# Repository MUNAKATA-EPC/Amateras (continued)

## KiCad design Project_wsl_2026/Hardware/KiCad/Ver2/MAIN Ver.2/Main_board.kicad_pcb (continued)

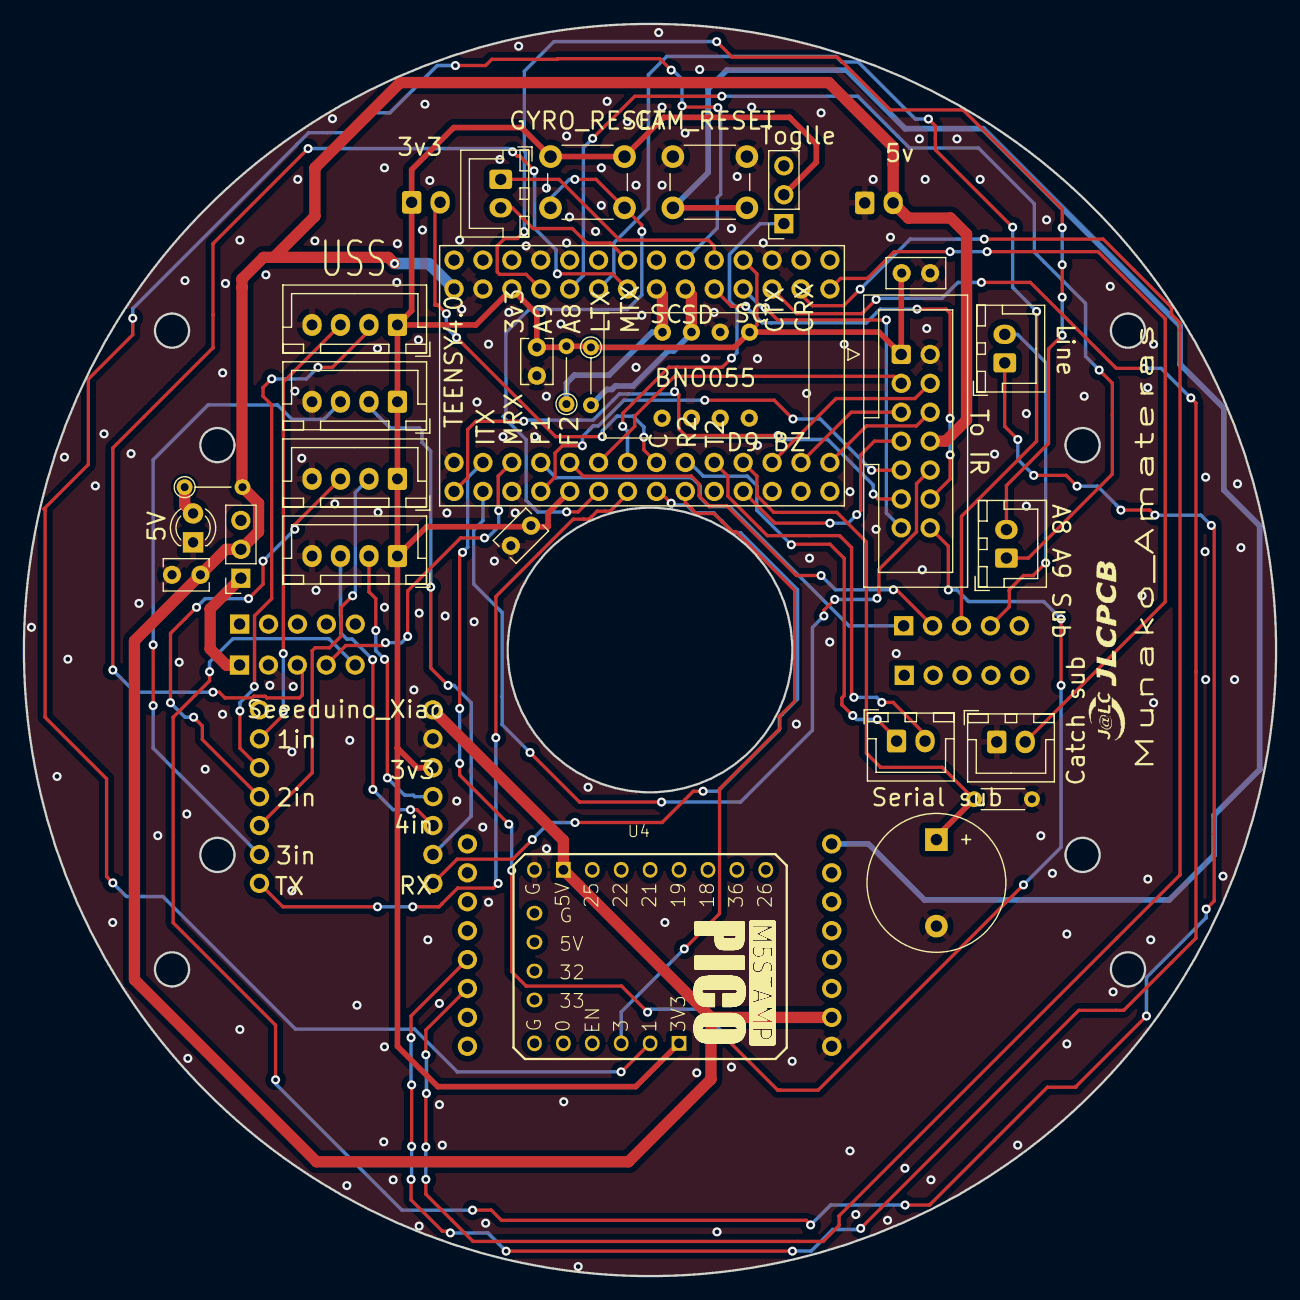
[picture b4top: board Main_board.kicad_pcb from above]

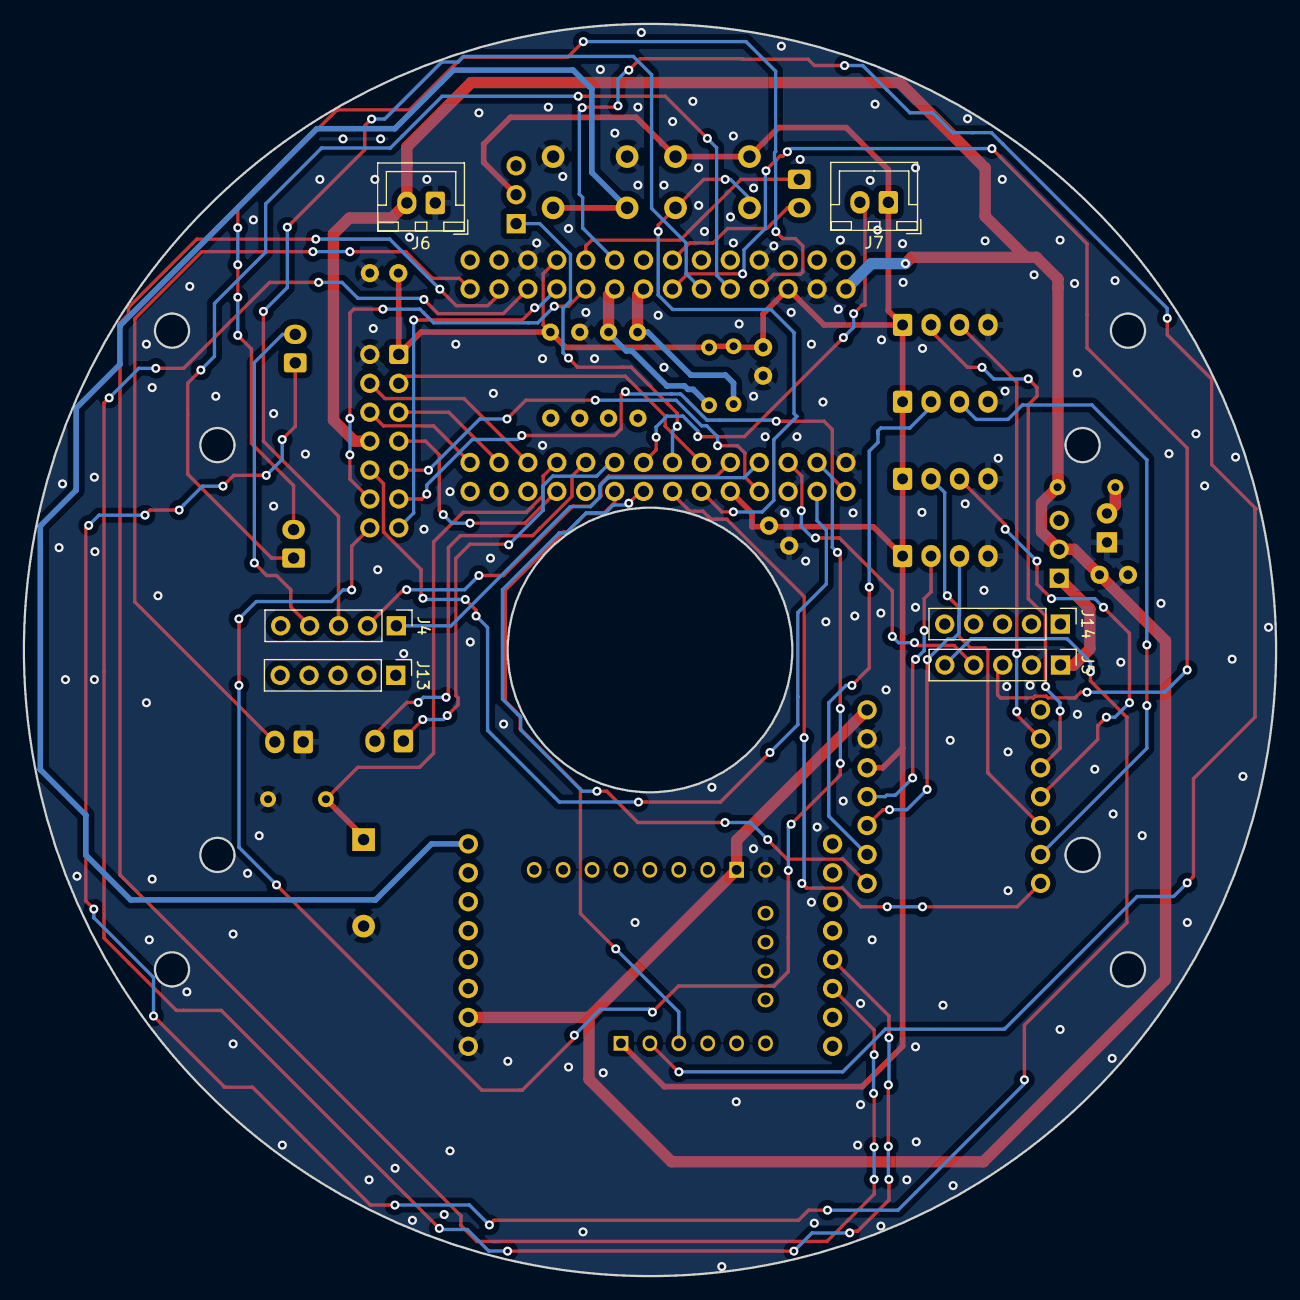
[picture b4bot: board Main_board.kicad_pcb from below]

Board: 2 copper layers, 110.0 x 110.0 mm, 35 parts (7 on the bottom side), 51 nets.

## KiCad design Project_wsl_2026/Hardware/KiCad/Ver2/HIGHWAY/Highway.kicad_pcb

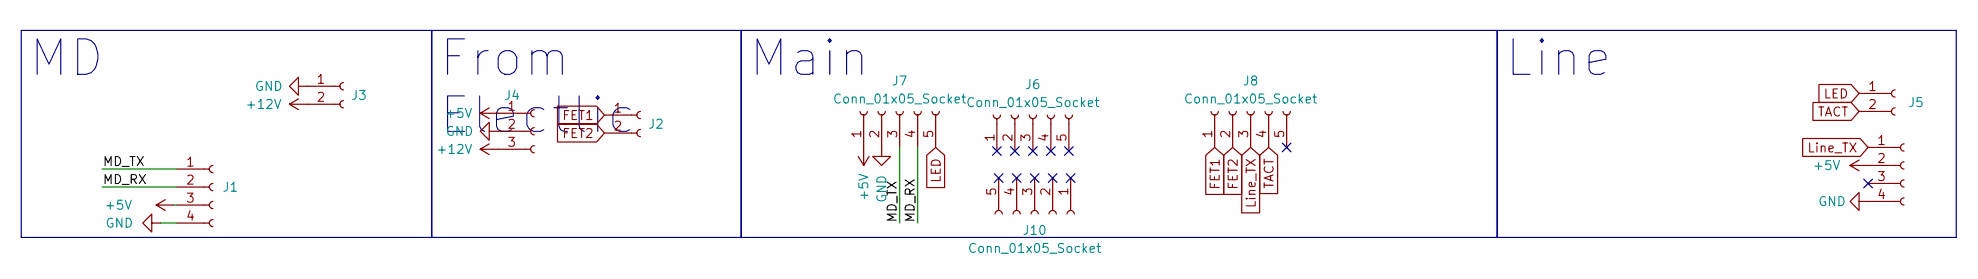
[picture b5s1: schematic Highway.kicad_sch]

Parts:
J1, J9: Conn_01x04_Socket; JST_XH_B4B-XH-A_1x04_P2.50mm_Vertical
J2, J3, J5: Conn_01x02_Socket; JST_XH_B2B-XH-A_1x02_P2.50mm_Vertical
J4: Conn_01x03_Socket; JST_XH_B3B-XH-A_1x03_P2.50mm_Vertical
J6, J7, J8, J10: Conn_01x05_Socket; PinSocket_1x05_P2.54mm_Vertical

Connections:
+5V: J1.3, J4.1, J7.1, J9.2
+12V: J3.2, J4.3
/MD_RX: J1.2, J7.4
/MD_TX: J1.1, J7.3
FET1: J2.1, J8.1
FET2: J2.2, J8.2
GND: J1.4, J3.1, J4.2, J7.2, J9.4
LED: J5.1, J7.5
Line_TX: J8.3, J9.1
TACT: J5.2, J8.4

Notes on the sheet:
From Electlic
Line
Main

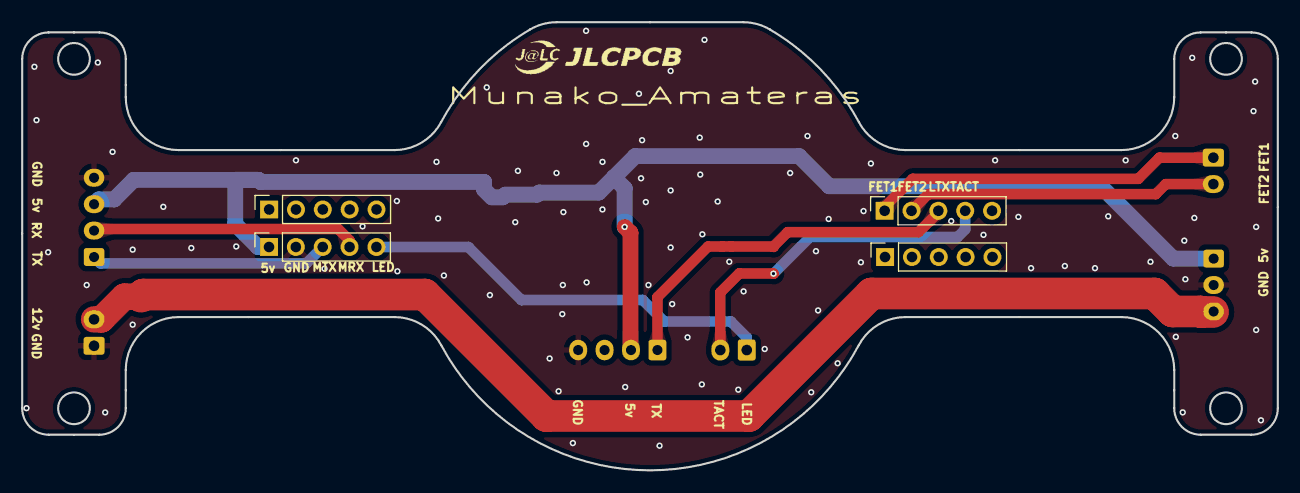
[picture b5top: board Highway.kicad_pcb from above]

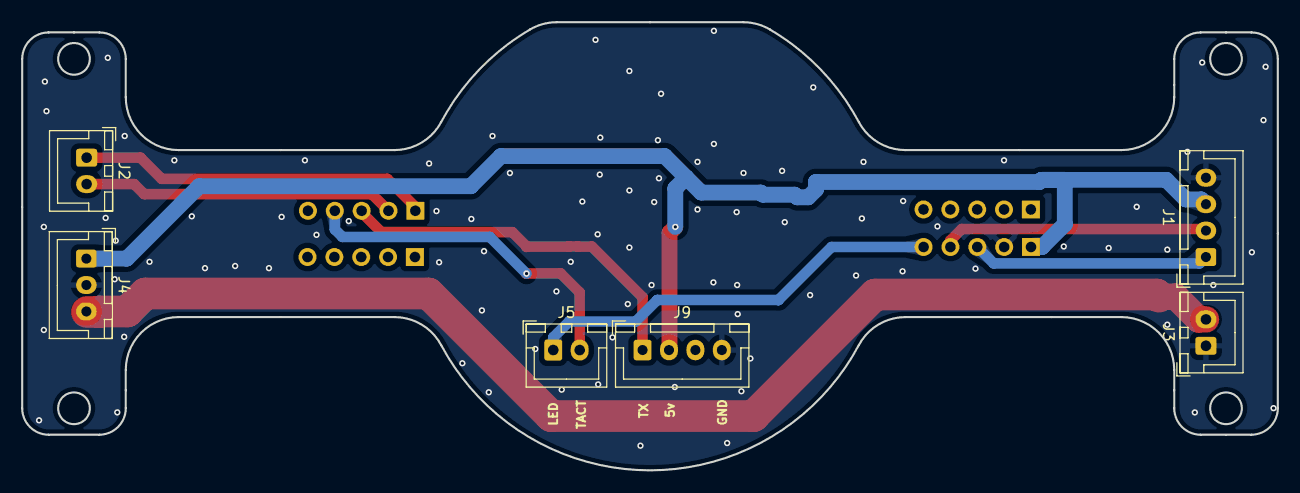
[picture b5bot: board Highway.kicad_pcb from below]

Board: 2 copper layers, 118.8 x 42.4 mm, 10 parts (6 on the bottom side), 10 nets.

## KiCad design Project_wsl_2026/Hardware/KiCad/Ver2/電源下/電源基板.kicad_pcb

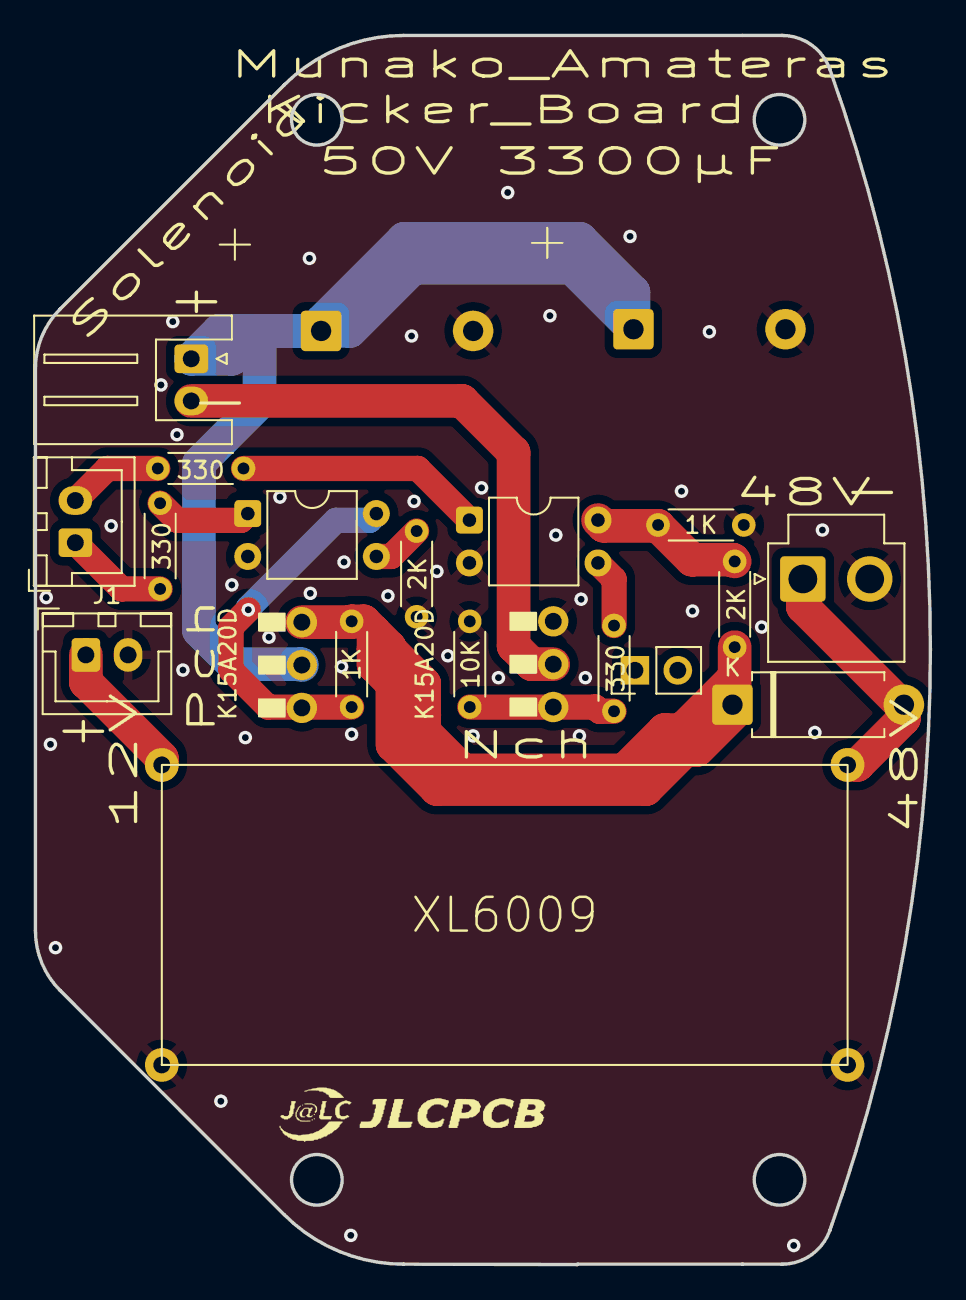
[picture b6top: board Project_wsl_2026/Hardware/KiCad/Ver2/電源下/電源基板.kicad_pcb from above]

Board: 2 copper layers, 53.0 x 72.8 mm, 21 parts (0 on the bottom side), 15 nets.

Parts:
1K, 1K#2: 1K; R_Axial_DIN0204_L3.6mm_D1.6mm_P5.08mm_Horizontal
2K, 2K#2: 2K; R_Axial_DIN0204_L3.6mm_D1.6mm_P5.08mm_Horizontal
10K: 10K; R_Axial_DIN0204_L3.6mm_D1.6mm_P5.08mm_Horizontal
330, 330#2, 330#3: 330; R_Axial_DIN0204_L3.6mm_D1.6mm_P5.08mm_Horizontal
C1, C4: C; 3300μF 50v
D2: D; D_DO-15_P10.16mm_Horizontal
FET: Conn_01x02_Socket; JST_XH_B2B-XH-A_1x02_P2.50mm_Vertical
J1: Conn_01x02_Socket; JST_XH_B2B-XH-A_1x02_P2.50mm_Vertical
J3: Conn_01x02_Socket; JST_VH_B2P-VH_1x02_P3.96mm_Vertical
J4: Conn_01x02_Socket; PinHeader_1x02_P2.54mm_Vertical
Q1: PMOS; K15A20D
Q2: NMOS; K15A20D
Solenoid: Conn_01x02_Socket; JST_XH_S2B-XH-A_1x02_P2.50mm_Horizontal
U2: XL6009
U3, U4: EL817; DIP-4_W7.62mm

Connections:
+12V: J1.1, U2.1 (IN＋)
+15V: 1K.1, 2K#2.2, U4.4
+48V: 1K#2.1, 2K#2.1, D2.1 (K), Q1.3 (S)
FET1: 330.1, FET.1
FET２: 330#3.1, FET.2
GND: 1K.2, 2K.2, 10K.2, C1.2, C4.2, J1.2, J3.2, Q2.3 (S), U2.2 (IN－), U2.4 (OUT－), U3.2, U4.2
unnamed: D2.2 (A), J3.1, U2.3 (OUT＋)
unnamed: 1K#2.2, Q1.2 (G), U3.4
unnamed: 10K.1, 330#2.1, Q2.2 (G)
unnamed: 330.2, U3.1
unnamed: 330#3.2, U4.1
unnamed: 2K.1, U3.3
unnamed: 330#2.2, U4.3
Solenoid+: C1.1, C4.1, Q1.1 (D), Solenoid.1
Solenoid-: Q2.1 (D), Solenoid.2

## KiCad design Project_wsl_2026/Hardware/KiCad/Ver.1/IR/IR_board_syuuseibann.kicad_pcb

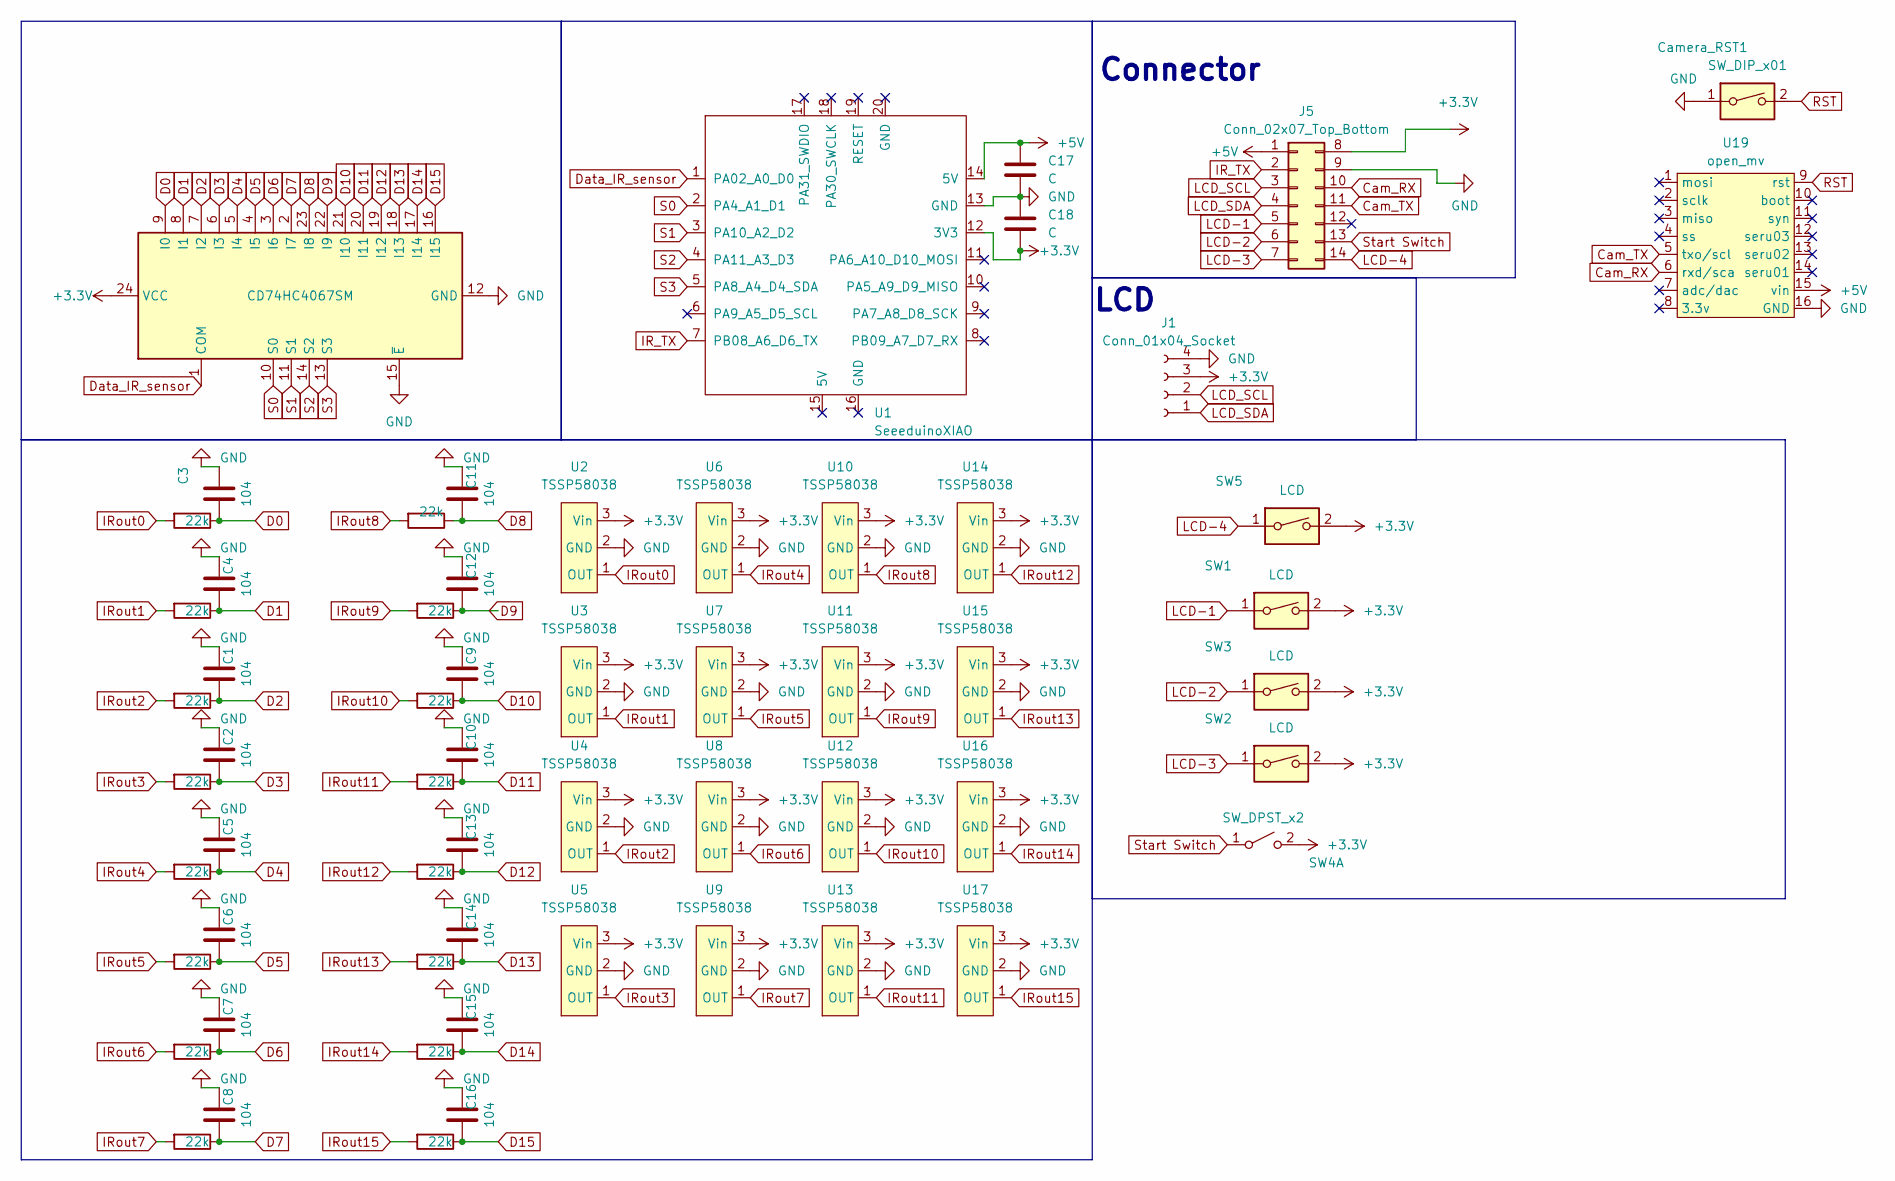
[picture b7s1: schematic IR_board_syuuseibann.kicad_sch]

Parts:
C1, C2, C3, C4, C5, C6, C7, C8, C9, C10, C11, C12, C13, C14, C15, C16: 104; C_0402_1005Metric; LCSC C1525
C17, C18: C; C_Disc_D5.0mm_W2.5mm_P2.50mm
Camera_RST1: SW_DIP_x01; SW_PUSH_6mm_H5mm
J1: Conn_01x04_Socket; PinHeader_1x04_P2.54mm_Vertical
J5: Conn_02x07_Top_Bottom; IDC-Header_2x07_P2.54mm_Vertical
R1, R2, R3, R4, R5, R6, R7, R8, R9, R10, R11, R12, R13, R14, R15, R16: 22k; R_0805_2012Metric; LCSC C25611
SW1, SW2, SW3, SW5: LCD; SW_PUSH_6mm_H5mm
SW4: SW_DPST_x2; PinSocket_1x03_P2.54mm_Vertical
U1: SeeeduinoXIAO; Seeeduino Xiao
U2, U3, U4, U5, U6, U7, U8, U9, U10, U11, U12, U13, U14, U15, U16, U17: TSSP58038; PinHeader_1x03_P2.54mm_Vertical
U18: CD74HC4067SM; SSOP-24_5.3x8.2mm_P0.65mm
U19: open_mv; Open MV

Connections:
+3.3V: C18.2, J1.3, J5.8, SW1.2, SW2.2, SW3.2, SW4.2 (B), SW5.2, U1.12 (3V3), U2.3 (Vin), U3.3 (Vin), U4.3 (Vin), U5.3 (Vin), U6.3 (Vin), U7.3 (Vin), U8.3 (Vin), U9.3 (Vin), U10.3 (Vin), U11.3 (Vin), U12.3 (Vin), U13.3 (Vin), U14.3 (Vin), U15.3 (Vin), U16.3 (Vin), U17.3 (Vin), U18.24 (VCC)
+5V: C17.1, J5.1, U1.14 (5V), U19.15 (vin)
Cam_RX: J5.10, U19.6 (rxd/sca)
Cam_TX: J5.11, U19.5 (txo/scl)
D0: C3.1, R3.1, U18.9 (I0)
D1: C4.1, R4.1, U18.8 (I1)
D2: C1.1, R1.1, U18.7 (I2)
D3: C2.1, R2.1, U18.6 (I3)
D4: C5.1, R5.1, U18.5 (I4)
D5: C6.1, R6.1, U18.4 (I5)
D6: C7.1, R7.1, U18.3 (I6)
D7: C8.1, R8.1, U18.2 (I7)
D8: C11.1, R11.1, U18.23 (I8)
D9: C12.1, R12.1, U18.22 (I9)
D10: C9.1, R9.1, U18.21 (I10)
D11: C10.1, R10.1, U18.20 (I11)
D12: C13.1, R13.1, U18.19 (I12)
D13: C14.1, R14.1, U18.18 (I13)
D14: C15.1, R15.1, U18.17 (I14)
D15: C16.1, R16.1, U18.16 (I15)
Data_IR_sensor: U1.1 (PA02_A0_D0), U18.1 (COM)
GND: C1.2, C2.2, C3.2, C4.2, C5.2, C6.2, C7.2, C8.2, C9.2, C10.2, C11.2, C12.2, C13.2, C14.2, C15.2, C16.2, C17.2, C18.1, Camera_RST1.1, J1.4, J5.9, U1.13 (GND), U2.2 (GND), U3.2 (GND), U4.2 (GND), U5.2 (GND), U6.2 (GND), U7.2 (GND), U8.2 (GND), U9.2 (GND), U10.2 (GND), U11.2 (GND), U12.2 (GND), U13.2 (GND), U14.2 (GND), U15.2 (GND), U16.2 (GND), U17.2 (GND), U18.12 (GND), U18.15 (~E), U19.16 (GND); also elsewhere on the board
IR_TX: J5.2, U1.7 (PB08_A6_D6_TX)
IRout0: R3.2, U2.1 (OUT)
IRout1: R4.2, U3.1 (OUT)
IRout2: R1.2, U4.1 (OUT)
IRout3: R2.2, U5.1 (OUT)
IRout4: R5.2, U6.1 (OUT)
IRout5: R6.2, U7.1 (OUT)
IRout6: R7.2, U8.1 (OUT)
IRout7: R8.2, U9.1 (OUT)
IRout8: R11.2, U10.1 (OUT)
IRout9: R12.2, U11.1 (OUT)
IRout10: R9.2, U12.1 (OUT)
IRout11: R10.2, U13.1 (OUT)
IRout12: R13.2, U14.1 (OUT)
IRout13: R14.2, U15.1 (OUT)
IRout14: R15.2, U16.1 (OUT)
IRout15: R16.2, U17.1 (OUT)
LCD-1: J5.5, SW1.1
LCD-2: J5.6, SW3.1
LCD-3: J5.7, SW2.1
LCD-4: J5.14, SW5.1
LCD_SCL: J1.2, J5.3
LCD_SDA: J1.1, J5.4
RST: Camera_RST1.2, U19.9 (rst); also elsewhere on the board
S0: U1.2 (PA4_A1_D1), U18.10 (S0)
S1: U1.3 (PA10_A2_D2), U18.11 (S1)
S2: U1.4 (PA11_A3_D3), U18.14 (S2)
S3: U1.5 (PA8_A4_D4_SDA), U18.13 (S3)
Start Switch: J5.13, SW4.1 (A)

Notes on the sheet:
LCD
Connector

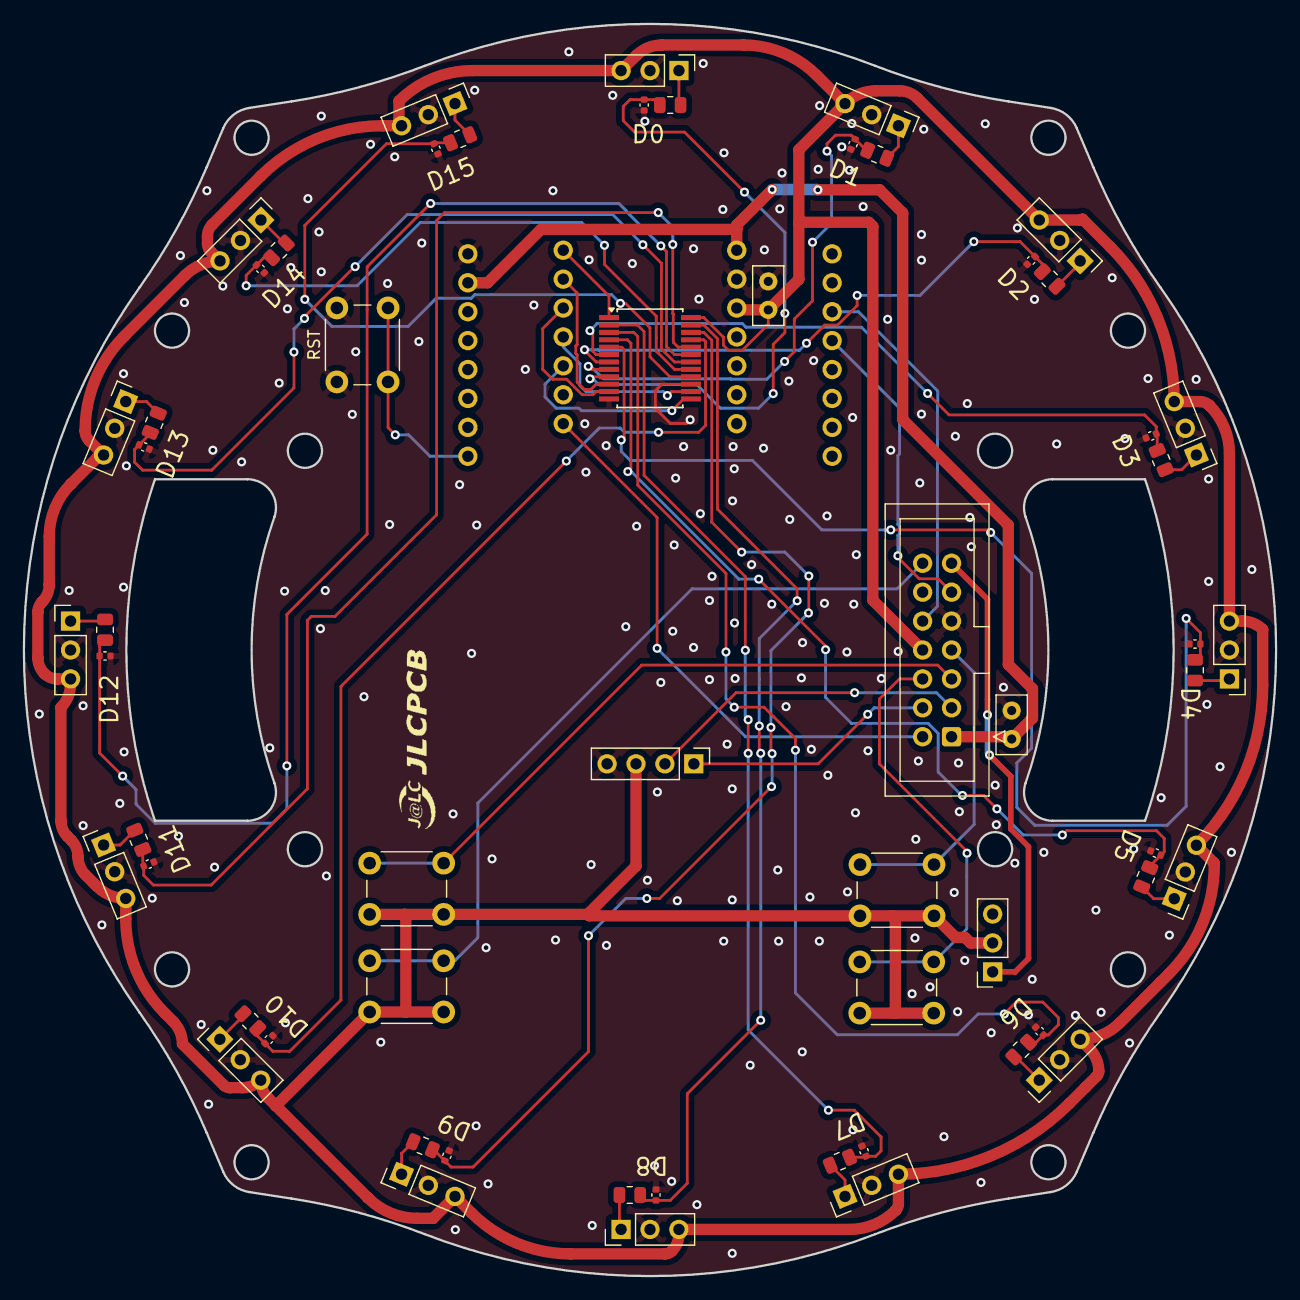
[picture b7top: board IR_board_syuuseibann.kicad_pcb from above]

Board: 2 copper layers, 110.0 x 110.0 mm, 61 parts (1 on the bottom side), 51 nets.

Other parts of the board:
RST: SW_DIP_x01; SW_PUSH_6mm_H5mm

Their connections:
GND: RST.1; also elsewhere on the board
RST: RST.2; also elsewhere on the board

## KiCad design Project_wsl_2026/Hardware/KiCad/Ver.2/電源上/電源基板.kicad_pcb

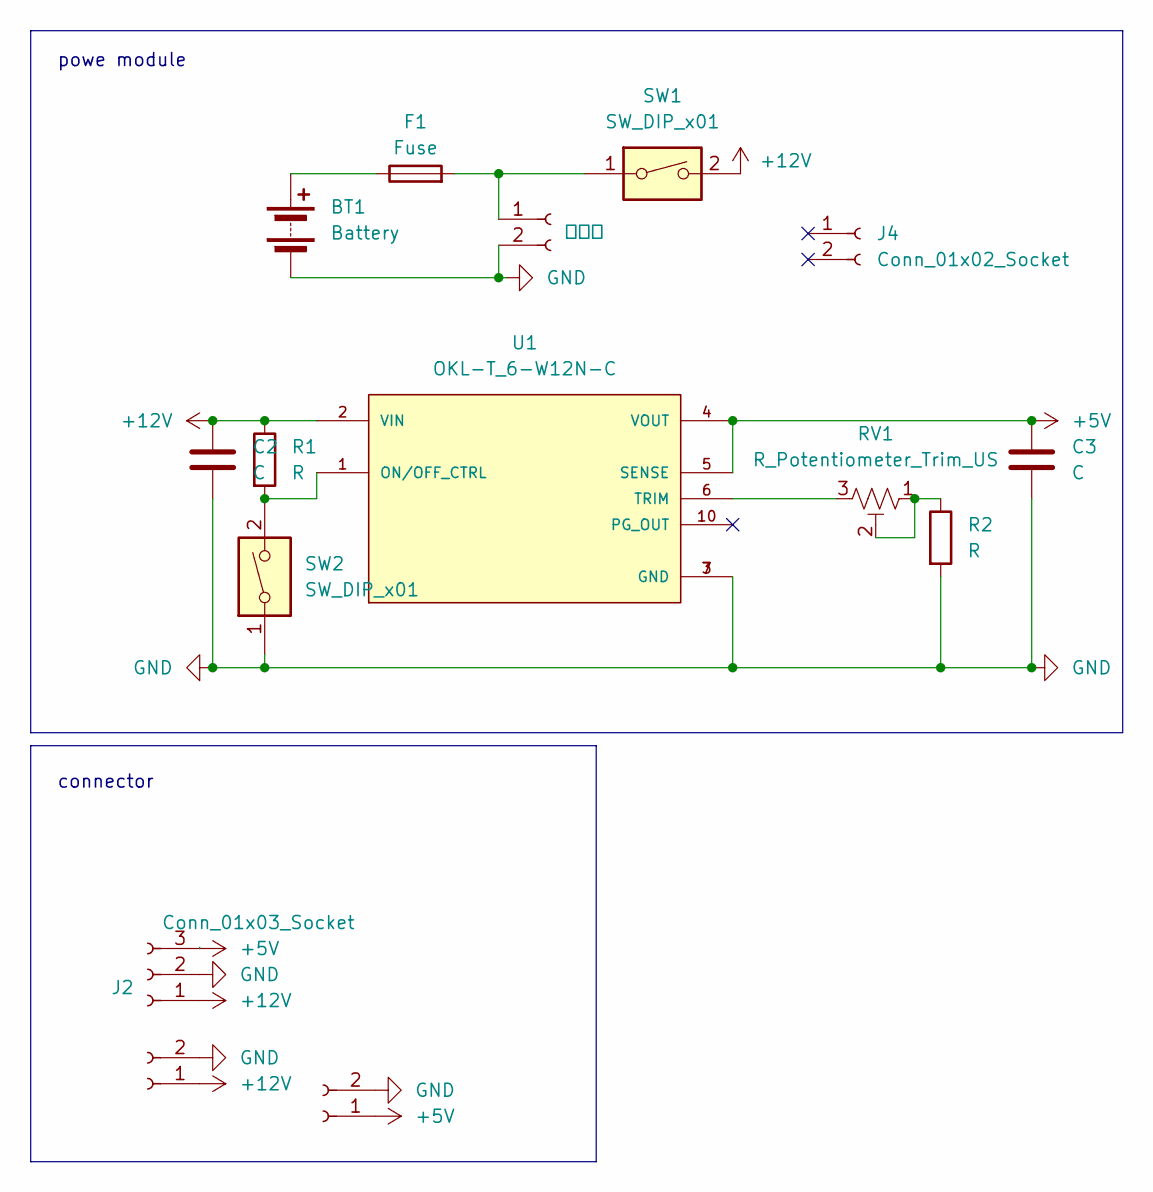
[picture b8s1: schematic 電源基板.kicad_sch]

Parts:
BT1: Battery; JST_VH_B2PS-VH_1x02_P3.96mm_Horizontal
C2, C3: C; C_Disc_D3.8mm_W2.6mm_P2.50mm
F1: Fuse; fuse_socket
J1: Conn_01x02_Socket; JST_XH_B2B-XH-A_1x02_P2.50mm_Vertical
J2: Conn_01x03_Socket; JST_XH_S3B-XH-A_1x03_P2.50mm_Horizontal
J3: Conn_01x02_Socket; JST_XH_S2B-XH-A_1x02_P2.50mm_Horizontal
J4: Conn_01x02_Socket; PinHeader_1x02_P2.54mm_Vertical
J6: 電圧計; JST_XH_S2B-XH-A_1x02_P2.50mm_Horizontal
R1, R2: R; R_Axial_DIN0204_L3.6mm_D1.6mm_P5.08mm_Horizontal
RV1: R_Potentiometer_Trim_US; Potentiometer_Bourns_3296W_Vertical
SW1: SW_DIP_x01; DS-850k
SW2: SW_DIP_x01; JST_XH_B3B-XH-A_1x03_P2.50mm_Vertical
U1: OKL-T_6-W12N-C; DCDC-murata-6A

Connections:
+5V: C3.1, J1.1, J2.3, U1.4 (VOUT), U1.5 (SENSE)
+12V: C2.1, J2.1, J3.1, R1.1, SW1.2, U1.2 (VIN)
GND: BT1.2 (-), C2.2, C3.2, J1.2, J2.2, J3.2, J6.2, R2.2, SW2.1, U1.3 (GND), U1.7 (GND)
unnamed: BT1.1 (+), F1.1
unnamed: F1.2, J6.1, SW1.1
unnamed: R2.1, RV1.1, RV1.2
unnamed: R1.2, SW2.2, U1.1 (ON/OFF_CTRL)
unnamed: RV1.3, U1.6 (TRIM)

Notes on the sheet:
powe module
connector

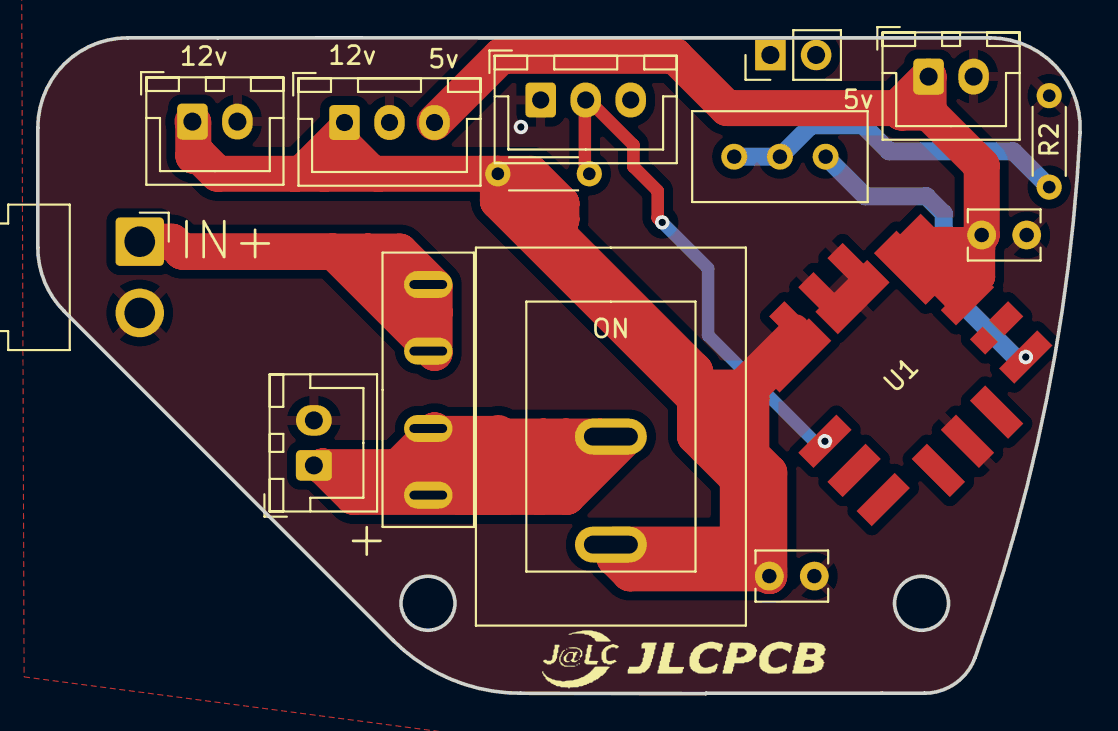
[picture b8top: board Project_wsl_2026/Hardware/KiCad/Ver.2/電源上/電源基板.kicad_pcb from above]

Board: 2 copper layers, 57.9 x 36.4 mm, 15 parts (0 on the bottom side), 8 nets.

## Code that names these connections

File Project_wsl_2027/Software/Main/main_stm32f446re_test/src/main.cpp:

#include <Arduino.h>
// action
#include "action/offence.hpp"
#include "action/defence.hpp"
// common
#include "common/serial_packet.hpp"
#include "common/bus_instance.hpp"
// device
#include "device/bno.hpp"
#include "device/button.hpp"
#include "device/led.hpp"
#include "device/toggle.hpp"
// module
#include "module/camera.hpp"
#include "module/lidar.hpp"
#include "module/line.hpp"
#include "module/ui.hpp"

extern "C" void SystemClock_Config(void)
{
  RCC_OscInitTypeDef RCC_OscInitStruct = {0};
  RCC_ClkInitTypeDef RCC_ClkInitStruct = {0};

  __HAL_RCC_PWR_CLK_ENABLE();
  __HAL_PWR_VOLTAGESCALING_CONFIG(PWR_REGULATOR_VOLTAGE_SCALE1);

  RCC_OscInitStruct.OscillatorType = RCC_OSCILLATORTYPE_HSE;
  RCC_OscInitStruct.HSEState = RCC_HSE_ON;
  RCC_OscInitStruct.PLL.PLLState = RCC_PLL_ON;
  RCC_OscInitStruct.PLL.PLLSource = RCC_PLLSOURCE_HSE;

  RCC_OscInitStruct.PLL.PLLM = 8;
  RCC_OscInitStruct.PLL.PLLN = 360;
  RCC_OscInitStruct.PLL.PLLP = RCC_PLLP_DIV2;
  RCC_OscInitStruct.PLL.PLLQ = 2;
  RCC_OscInitStruct.PLL.PLLR = 2;

  if (HAL_RCC_OscConfig(&RCC_OscInitStruct) != HAL_OK)
  {
    while (1)
      ;
  }

  if (HAL_PWREx_EnableOverDrive() != HAL_OK)
  {
    while (1)
      ;
  }

  RCC_ClkInitStruct.ClockType = RCC_CLOCKTYPE_HCLK | RCC_CLOCKTYPE_SYSCLK | RCC_CLOCKTYPE_PCLK1 | RCC_CLOCKTYPE_PCLK2;
  RCC_ClkInitStruct.SYSCLKSource = RCC_SYSCLKSOURCE_PLLCLK;
  RCC_ClkInitStruct.AHBCLKDivider = RCC_SYSCLK_DIV1;
  RCC_ClkInitStruct.APB1CLKDivider = RCC_HCLK_DIV4;
  RCC_ClkInitStruct.APB2CLKDivider = RCC_HCLK_DIV2;

  if (HAL_RCC_ClockConfig(&RCC_ClkInitStruct, FLASH_LATENCY_5) != HAL_OK)
  {
    while (1)
      ;
  }
}

void setup()
{
  // m5
  mySerial3.begin(115200);
  ui::attach(mySerial3);

  // pc
  mySerial2.begin(115200);

  // btn
  left_btn.begin(PC11, INPUT_PULLDOWN);
  right_btn.begin(PB15, INPUT_PULLDOWN);

  // toggle
  action_toggle.begin(PB14, INPUT_PULLDOWN);
  // led
  red_led.begin(PB5);
  yellow_led.begin(PA11);
  green_led.begin(PC8);
}

void loop()
{
  // btn・toggle・led更新
  static uint32_t last_time = 0;
  if (millis() - last_time > 100)
  {
    left_btn.update();
    right_btn.update();
    action_toggle.update();

    red_led.light(ui::cur_state != ui::STATE::HOME);

    if (ui::ACTION::run)
    {
      yellow_led.light(right_btn.isPushing() || left_btn.isPushing());
      green_led.lightup();
    }
    else
    {
      switch (ui::cur_state)
      {
      case ui::STATE::HOME:
        green_led.lightdown();
        yellow_led.lightdown();
        break;
      case ui::STATE::TEST_KICKER:
        green_led.light(ui::TEST_KICKER::btn);
        yellow_led.light(ui::TEST_KICKER::front);
        break;
      case ui::STATE::TEST_DRIBBLER:
        green_led.light(ui::TEST_DRIBBLER::toggle);
        yellow_led.light(ui::TEST_DRIBBLER::front);
        break;
      case ui::STATE::TEST_MOTOR:
        green_led.light(ui::TEST_MOTOR::toggle);
        yellow_led.light(right_btn.isPushing() || left_btn.isPushing());
        break;
      default:
        yellow_led.lightdown();
        green_led.lightdown();
        break;
      }
    }

    last_time = millis();
  }

  // camera更新
  camera::process(ui::ACTION::meter_type);
  // lidar更新
  lidar::process();
  // line更新
  line::process();
  // ui更新
  ui::process(action_toggle.isTurnedOn());

  // action実行
  if (ui::ACTION::run)
  {
    switch (ui::cur_state)
    {
    case ui::STATE::ACTION_OFFENCE:
      offence();
      break;
    case ui::STATE::ACTION_DEFENCE:
      defence();
      break;
    case ui::STATE::ACTION_RADIOCONTROL:
      break;
    }
  }
}

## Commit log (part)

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2026-06-25 Create IR
2026-06-27 Create IRa
